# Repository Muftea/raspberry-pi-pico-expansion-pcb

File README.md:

# raspberry-pi-pico-expansion-pcb
Custom two-layer Raspberry Pi Pico expansion PCB designed in KiCad for embedded systems prototyping.

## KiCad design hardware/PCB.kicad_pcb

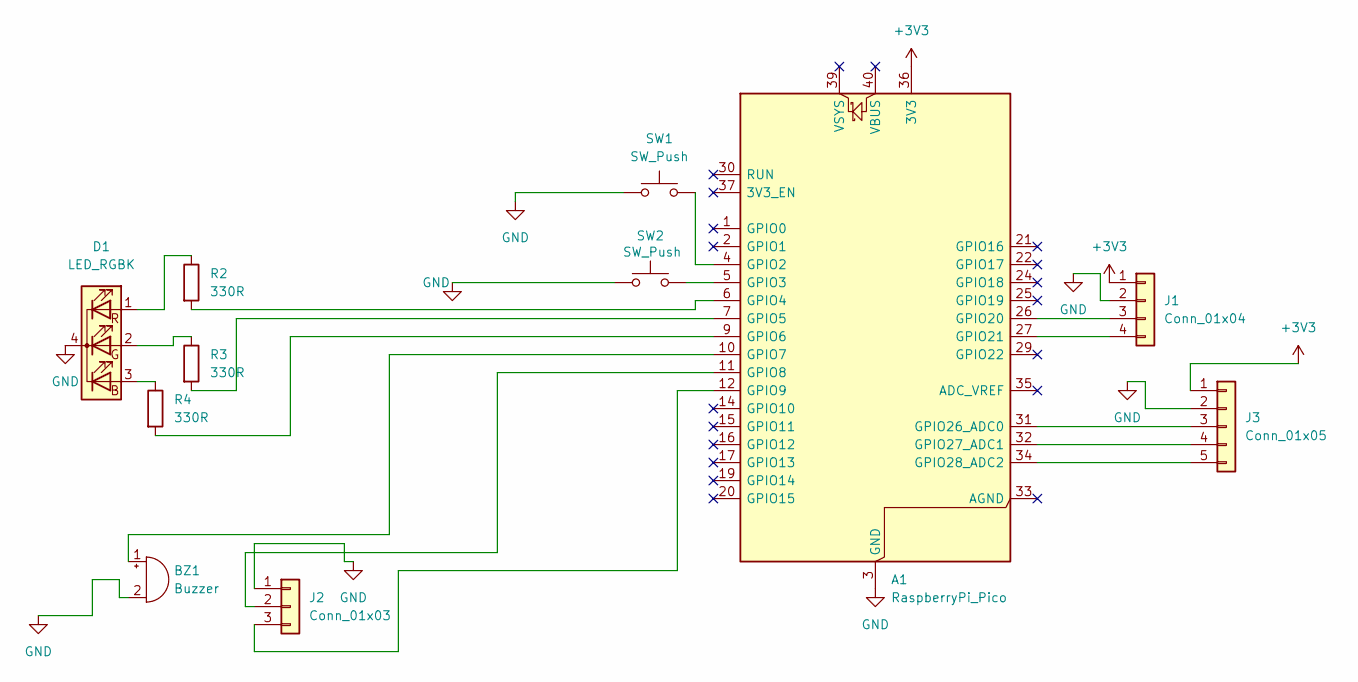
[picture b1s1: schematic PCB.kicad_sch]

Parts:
A1: RaspberryPi_Pico; RaspberryPi_Pico_Common_Unspecified
BZ1: Buzzer; Buzzer_12x9.5RM7.6
D1: LED_RGBK; LED_D5.0mm-4_RGB
J1: Conn_01x04; PinHeader_1x04_P2.54mm_Vertical
J2: Conn_01x03; PinHeader_1x03_P2.54mm_Vertical
J3: Conn_01x05; PinHeader_1x05_P2.54mm_Vertical
R2, R3, R4: 330R; R_Axial_DIN0207_L6.3mm_D2.5mm_P7.62mm_Horizontal
SW1, SW2: SW_Push; SW_PUSH_6mm

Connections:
+3V3: A1.36 (3V3), J1.1, J3.1
GND: A1.3 (GND), A1.8 (GND), A1.13 (GND), A1.18 (GND), A1.23 (GND), A1.28 (GND), A1.38 (GND), BZ1.2 (-), D1.4 (K), J1.2, J2.1, J3.2, SW1.1, SW2.1
unnamed: A1.4 (GPIO2), SW1.2
unnamed: A1.5 (GPIO3), SW2.2
unnamed: A1.6 (GPIO4), R2.2
unnamed: A1.7 (GPIO5), R3.2
unnamed: A1.9 (GPIO6), R4.2
unnamed: A1.10 (GPIO7), BZ1.1 (+)
unnamed: A1.11 (GPIO8), J2.2
unnamed: A1.12 (GPIO9), J2.3
unnamed: A1.26 (GPIO20), J1.3
unnamed: A1.27 (GPIO21), J1.4
unnamed: A1.31 (GPIO26_ADC0), J3.3
unnamed: A1.32 (GPIO27_ADC1), J3.4
unnamed: A1.34 (GPIO28_ADC2), J3.5
unnamed: D1.3 (BA), R4.1
unnamed: D1.2 (GA), R3.1
unnamed: D1.1 (RA), R2.1

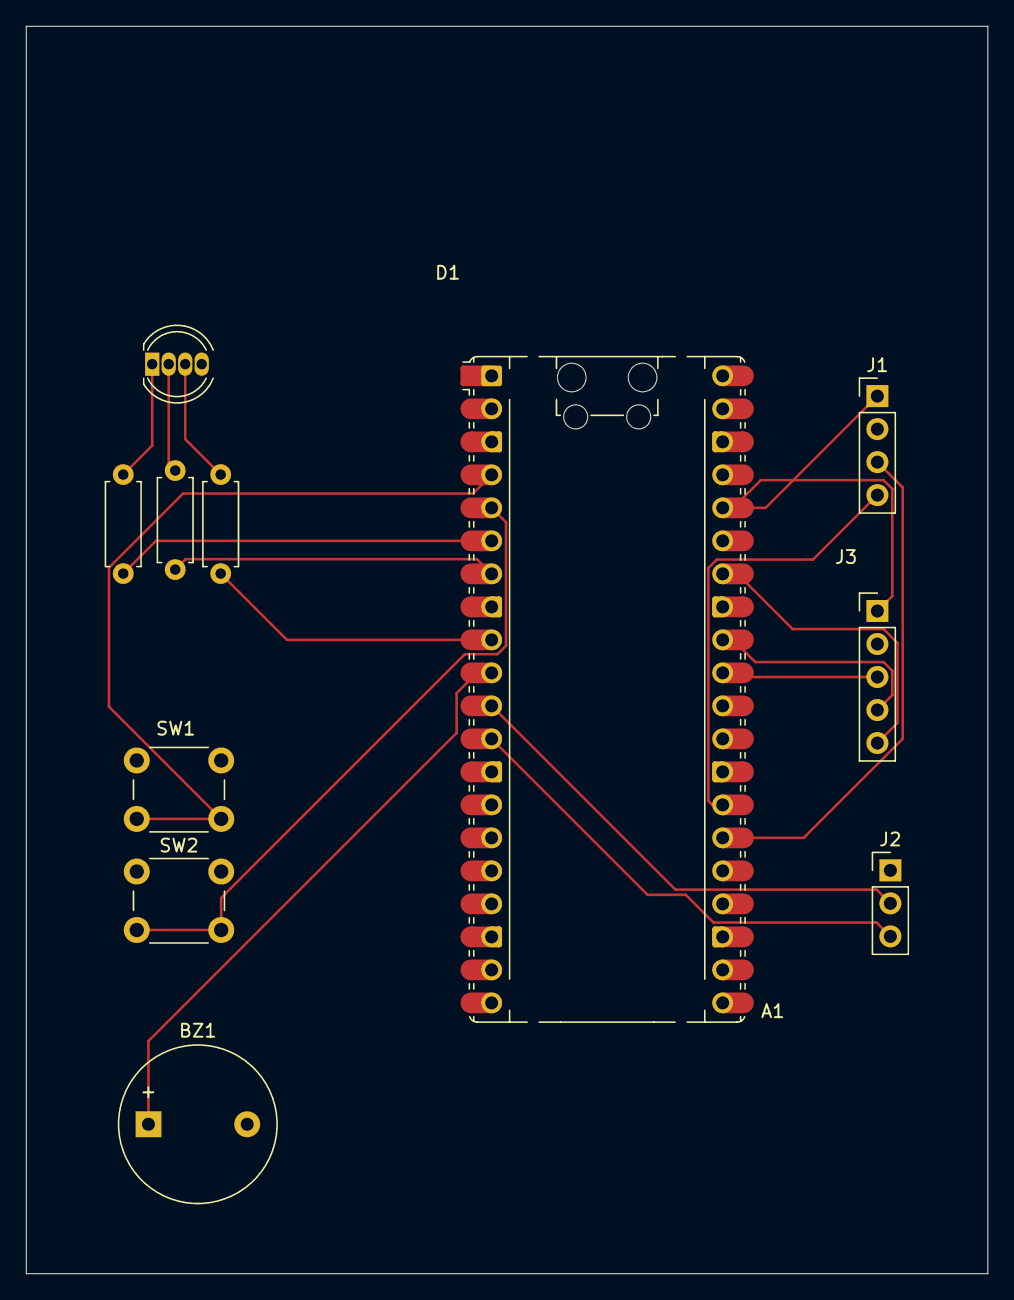
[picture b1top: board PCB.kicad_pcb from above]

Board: 2 copper layers, 74.0 x 96.0 mm, 11 parts (0 on the bottom side), 18 nets.
